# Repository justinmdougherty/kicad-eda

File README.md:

# dougherty-eda — Claude Code marketplace

Plugins for electronic design automation.

```
/plugin marketplace add justinmdougherty/kicad-eda
/plugin install kicad-eda@dougherty-eda
/kicad-eda:setup        # checks/installs KiCad, Java, Python
```

**New to all of this?** Start with the step-by-step
[setup guide](kicad-eda/docs/SETUP.md) — it assumes nothing and takes you
from a blank machine to your first board.

- **kicad-eda** — design circuit boards by chatting with Claude: describe the
  board, get back an ERC-clean schematic, a placed + autorouted PCB with
  clean DRC, and a fab-ready zip (Gerbers, drill, BOM, CPL). Five
  self-remediating review gates in the IEEE 15288.2 style do the engineering
  discipline; KiCad 10 + the bundled Freerouting autorouter do the file
  work, and an optional KiCad 11 nightly lets KiCad draw the schematic
  itself through its IPC API. See [`kicad-eda/README.md`](kicad-eda/README.md) to get started and
  [`kicad-eda/docs/PIPELINE.md`](kicad-eda/docs/PIPELINE.md) for the
  internals run-book.

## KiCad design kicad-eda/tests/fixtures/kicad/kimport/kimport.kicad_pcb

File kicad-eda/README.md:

# kicad-eda — Napkin to Gerbers

A Claude Code plugin that designs circuit boards **in conversation**. You
describe the board you want — what it does, how it's powered, what it
connects to — and Claude carries it from concept to a fab-ready zip:
schematic with clean ERC, placed and routed PCB with clean DRC (Claude
routes it net by net through KiCad's board API, or Freerouting does),
Gerbers, drill, BOM and placement files you can upload straight to JLCPCB.

```
You:    I need a USB-C powered 3-channel LED driver, 1.5 A per channel.
Claude: <asks the questions an engineer would, then designs it>
        … G1 requirements ✓  G2 schematic+ERC ✓  G3 placement ✓
        G4 routed, DRC 0/0 ✓  G5 fab package ✓ → led_driver_JLCPCB.zip
```

The work runs through **five formal review gates** (IEEE 15288.2 style) that
**self-remediate**: missing bypass caps get added, placement loosens itself
when routing is congested, routing micro-gaps and split power planes are
healed, under-ampacity layer transitions get parallel vias, dissipating
power packages get IPC-7093 thermal via farms. You only get asked when a
decision genuinely needs design intent.

## Install

> **First time? Never used Claude Code or cloned a repo?** Follow
> **[docs/SETUP.md](docs/SETUP.md)** — a step-by-step guide from a blank
> machine to your first board, no prior knowledge assumed.

```
/plugin marketplace add justinmdougherty/kicad-eda
/plugin install kicad-eda@dougherty-eda
```

Then run **`/kicad-eda:setup`** once — it checks the three external
dependencies and installs what's missing:

| Dependency | Used for | Windows | macOS |
|---|---|---|---|
| KiCad 10 | kicad-cli, bundled pcbnew Python, stock libraries | `winget install KiCad.KiCad` | `brew install --cask kicad` |
| KiCad 11 nightly *(optional)* | schematic API backend: KiCad draws the schematic itself, headless or live in its editor | [nightly installer](https://downloads.kicad.org/kicad/windows/explore/nightlies) (lands in `Program Files\KiCad\10.99`) | nightly `.dmg` from the same site |
| Java 17–21 | Freerouting 1.9.0 autorouter (jar is bundled) | `winget install EclipseAdoptium.Temurin.21.JRE` | `brew install --cask temurin@21` |
| Python 3.10+ | MCP server + pipeline harness | `winget install Python.Python.3.12` | `brew install python` |

Python *packages* need nothing: the server launcher
(`scripts/launch-server.js`) builds its own venv on first start and keeps it
in the plugin data dir, surviving updates. `setup` only reports the KiCad 11
nightly; it never installs it.

## Usage

Just talk to Claude about the board you want, or jump straight in:

```
/kicad-eda:pipeline a USB-C powered 3-channel LED driver, 1.5 A per channel
/kicad-eda:new-board ...     # GUI-assisted flow in the KiCad editor instead
```

You get back the full project: `netlist.json` (the design's source of
truth), `.kicad_sch`, `.kicad_pcb` (open them in KiCad), top/bottom renders
to eyeball, a design-intent report, and the fab zip.

Under the hood the conversation produces a pad-level `netlist.json`, and the
headless pipeline does the rest — schematic + ERC (through KiCad 11's
schematic API when a nightly is installed, else the plugin writes the file
itself), SWIG board build (placement, planes, preroutes, silk), routing,
DRC + IPC-2221/2141A checks, Gerber/BOM/CPL export. Power users can
author or edit `netlist.json` directly and run
`/kicad-eda:pipeline path/to/netlist.json`; the schema, gate map and the
schematic-backend rules live in **`docs/PIPELINE.md`** (the run-book).

**Routing is Claude's job, not an autorouter's.** With a KiCad 11 nightly
installed (or the board open in a running KiCad with its API server on),
Claude routes the placed board itself through KiCad's board API: it reads
pads, net classes, planes and the foreign copper near every unrouted link,
lays tracks and vias net by net, and clears real kicad-cli DRC in a repair
loop (`agent-routing` skill, `router` subagent). The tools:
`open_board`, `board_overview`, `board_pads`, `unrouted_connections`,
`route_net`, `add_vias`, `remove_routing`, `route_check`, `route_status`,
`save_board`, `close_board`, `list_open_boards`. Freerouting
(`autoroute_board`) stays as the fallback and is what the unattended
`run_pipeline.py` harness runs. One consequence to know: a board saved by the
headless KiCad 11 session becomes a **KiCad 11 file** — KiCad 9/10, their
kicad-cli/pcbnew and the Freerouting/SWIG tools cannot read it afterwards
(DRC and Gerbers still work through kicad-cli 11), so open it in KiCad 11.

## What's inside

| Component | What it does |
|---|---|
| `server/` | The `kicad-generator` MCP server (`kicad_env` finds every installed KiCad and picks one per job — board jobs follow the KiCad that wrote the file; `backends/` is the KiCad 11 IPC schematic backend and the board API backend (`pcb_api`) on the vendored `vendor/kipy`; `route_planner` + `board_route_tools` are the agent-routing geometry and tools; `sch_file_model` is the schematic file-writing fallback) + the toolchain it shells into: `sch_build` (ERC-clean schematics without KiCad 11), `swig_build_board` (placement/planes/preroutes/silk under KiCad's bundled Python), `netclass_writer` + `ipc_rules` (IPC-2221/2141A math), `swig_gate_checks` (placement/thermal/plane/height/routed-width/via-ampacity reviews), `swig_board_fixes` (auto-remediation incl. a BFS maze router), `silk_place`, `gates` + `remediate` (the review system), and `freerouting-1.9.0.jar`. |
| `pipeline/` | `run_pipeline.py` (one board through all five gates) and `run_all.py` (the developer regression suite over `examples/`). |
| `examples/` | Test netlists used to validate the process (QFN, LQFP, multi-unit op-amps, a 3 A buck, RF boards, an ESP32-C3 node, a two-sided RPi 5 HAT). Useful as schema references; not end-user content. |
| `docs/PIPELINE.md` | The run-book: netlist schema, gate map, env vars, and the known-traps list that costs real hours to rediscover. |
| `skills/` | `netlist-pipeline` (headless flow), `pcb-design` (GUI flow) and `agent-routing` (how Claude routes a board through the KiCad board API). |
| `agents/` | Gate reviewers: `parts-selector`, `erc-reviewer`, `placement-reviewer`, `drc-reviewer`, `fab-checker`; and `router`, the routing specialist that runs the route / DRC / repair loop. |
| `commands/` | `/setup`, `/pipeline`, `/new-board`, `/erc`, `/drc`, `/gerbers`. |
| `hooks/` | Cross-platform (Node): session env report, IPC-API guard for GUI tools, schematic structure check after writes. |

## Requirements

- **Claude Code or Claude Desktop** (local MCP server — not the web app).
- KiCad 10, Java 17–21, Python 3.10+ (see Install). KiCad 9 mostly works
  but the headless pipeline is validated against 10.
- **Optional: a KiCad 11 nightly** from
  <https://downloads.kicad.org/kicad/windows/explore/nightlies>. It installs
  beside KiCad 10 as `Program Files\KiCad\10.99` and enables the schematic
  API backend (`server_status().schematic_backend == "api"`) and the headless
  board API for agent routing (`server_status().board_api`). Open it once
  after installing — or copy `sym-lib-table` and `fp-lib-table` from
  `<install>\share\kicad\template` into `%APPDATA%\kicad\10.99` — or the
  headless server finds no libraries. Keep KiCad 10 for the board build (the
  nightly has no bundled pcbnew Python). Schematics and boards it saves are
  KiCad 11 files; KiCad 9/10 cannot open them (board DRC/Gerbers then run
  through the nightly's kicad-cli automatically).
- The headless pipeline never needs the KiCad GUI. The GUI flow's PCB tools
  require KiCad running with **Preferences → API → Enable KiCad API server**;
  with KiCad 11 the schematic tools also work live in the open editor.

## Developing

```bash
claude plugin validate ./kicad-eda --strict
node scripts/launch-server.js          # run the MCP server by hand
.venv/bin/python -m pytest -q          # unit tier (+ live KiCad 11 API tests when a nightly is present)
.venv/bin/python pipeline/run_all.py   # regression matrix (routes for many minutes)
docker build -t kicad-eda . && docker run --rm kicad-eda   # suite in the official KiCad container
```

CI runs the same regression suite on every push (`.github/workflows/regression.yml`).

## License

MIT

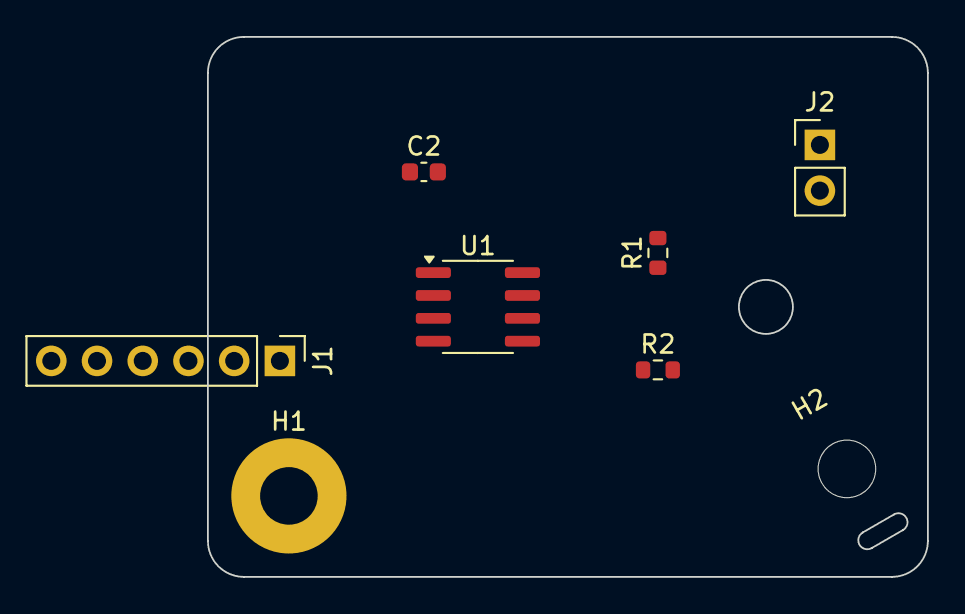
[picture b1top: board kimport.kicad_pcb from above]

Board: 2 copper layers, 40.0 x 30.0 mm, 9 parts (1 on the bottom side), 7 nets, no tracks yet.

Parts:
C1: 100nF; C_0603_1608Metric
C2: 1uF; C_0603_1608Metric
H1: MountingHole_3.2mm_M3_Pad
H2: MountingHole_3.2mm_M3
J1: IO; PinHeader_1x06_P2.54mm_Vertical
J2: AUX; PinHeader_1x02_P2.54mm_Vertical
R1: 1k; R_0603_1608Metric
R2: 10k; R_0603_1608Metric
U1: LM358; SOIC-8_3.9x4.9mm_P1.27mm

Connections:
/GND: C1.2, C2.2, H1.1, J1.2, J2.1, R2.2, U1.4
/IN_A: J1.3, R1.1
/IN_A_R: R1.2, U1.3
/IN_B: J1.5, R2.1, U1.5
/OUT_A: J1.4, U1.1, U1.2
/OUT_B: U1.6, U1.7
/P5V: C1.1, C2.1, J1.1, U1.8

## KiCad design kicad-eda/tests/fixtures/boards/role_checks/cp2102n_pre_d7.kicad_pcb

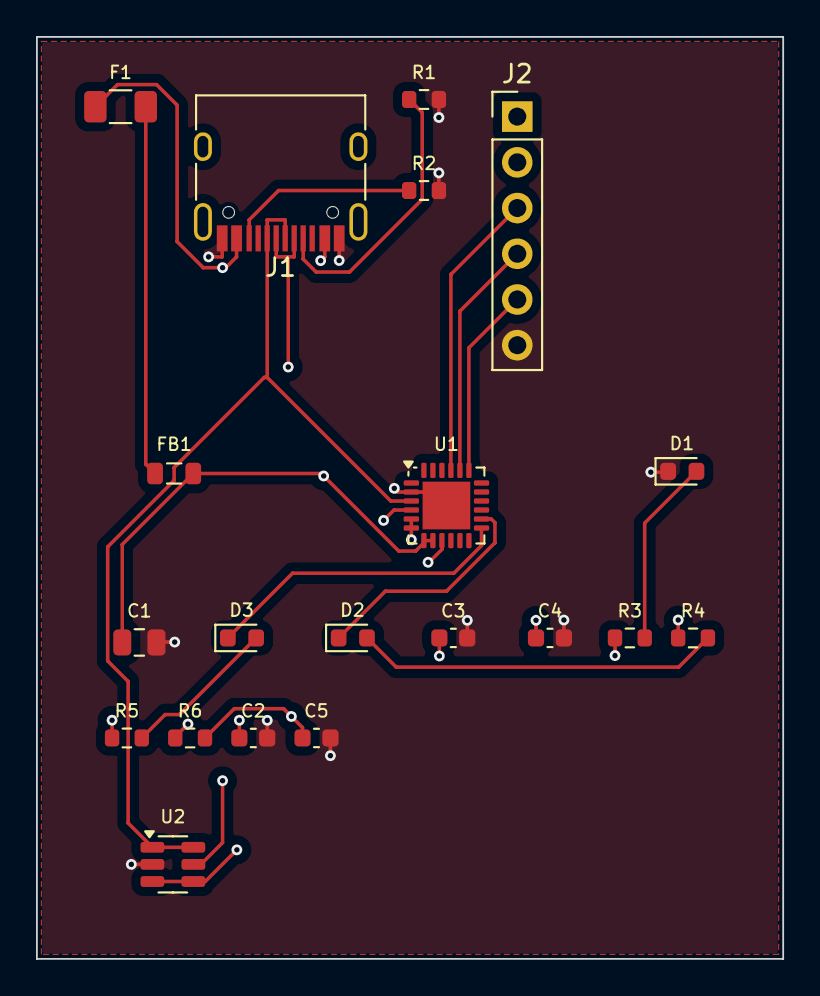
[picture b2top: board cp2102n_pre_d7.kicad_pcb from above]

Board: 4 copper layers, 41.5 x 51.2 mm, 20 parts (0 on the bottom side), 18 nets.

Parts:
C1: 4.7uF; C_0805_2012Metric
C2, C5: 1uF; C_0603_1608Metric
C3, C4: 100nF; C_0603_1608Metric
D1: PWR_GRN; LED_0603_1608Metric
D2: TX_YEL; LED_0603_1608Metric
D3: RX_GRN; LED_0603_1608Metric
F1: 500mA; Fuse_1206_3216Metric
FB1: 600R@100MHz; L_0805_2012Metric
J1: USB-C; USB_C_Receptacle_HRO_TYPE-C-31-M-12
J2: UART; PinHeader_1x06_P2.54mm_Vertical
R1, R2: 5.1k; R_0603_1608Metric
R3, R4, R5: 1k; R_0603_1608Metric
R6: 10k; R_0603_1608Metric
U1: CP2102N-A02-QFN24; QFN-24-1EP_4x4mm_P0.5mm_EP2.65x2.65mm
U2: USBLC6-2SC6; SOT-23-6

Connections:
+3V3: C2.1, C3.1, C4.1, J2.2, R3.1, R4.1, R5.1, R6.1, U1.5, U1.6
CC1: J1.A5, R1.1
CC2: J1.B5, R2.1
GND: C1.2, C2.2, C3.2, C4.2, C5.2, D1.1, J1.A1, J1.A12, J1.B1, J1.B12, J2.6, R1.2, R2.2, U1.2, U1.25, U2.2
PWR_LED_A: D1.2, R3.2
RST: C5.1, R6.2, U1.9
RTS: J2.5, U1.19
RXD: J2.4, U1.20
RXT_N: D3.1, U1.13
RX_LED_A: D3.2, R5.2
TXD: J2.3, U1.21
TXT_N: D2.1, U1.14
TX_LED_A: D2.2, R4.2
USB_DM: J1.A7, J1.B7, U1.4, U2.3, U2.4
USB_DP: J1.A6, J1.B6, U1.3, U2.1, U2.6
VBUS: F1.1, J1.A4, J1.A9, J1.B4, J1.B9, U2.5
VBUS_F: F1.2, FB1.1
VBUS_IN: C1.1, FB1.2, J2.1, U1.7, U1.8

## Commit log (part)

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2026-06-11 chore: baseline - gated headless pipeline, plugin packaging v0.2.0
2026-06-11 feat: thermal gate - dissipation vs package limits (G2) + EP via-farm check (G3)
    thermal_check.py: shunt I2R vs derated rating, FET conduction loss,
    linear-reg (Vin-Vout)*I, switcher loss estimate; Tj vs 80% Tj_max.
    Declared values block, estimates warn; per-part thermal overrides
    (p_diss/theta_ja/tj_max/i_max). G3 verifies >=4 thermal vias under
    dissipating exposed pads (IPC-7093). Example specs corrected where the
    gate caught real errors (AP2112K SOT-23-5 at 0.5A, LNA bias R at 4x
2026-06-11 feat: pre-route plane integrity check at G3
    Per plane net: union-find over fill islands + pads + preroute copper.
    True multi-island pad split = blocker (DSN export hides voids, router
    returns the net broken). Pinch corridors <1.8mm between pad groups
    (one router via from sealing) = warning, GND exempt (post-route pours
    own its unification). Pad-to-island attach uses true polygon distance
    (bbox distance is meaningless for a board-spanning outline). Gate
2026-06-11 feat: height keepout zones at G3 (mechanical ceiling)
    netlist height_zones: per-region max_height with side F/B/both and
    exempt list; part height from component 'height' or a package table.
    Over-ceiling = blocker, unknown-height-in-zone = warning. HAT example
    gains a 4mm B-side ceiling (clearance to the Pi) exempting J5.
2026-06-11 feat: diff-pair declaration + routed-as-pair flagging at G4
    net_specs {'diff_pair': partner, dp_tol_mm, dp_gap_mm}: measures
    intra-pair length mismatch and coupled-length fraction (<70% flags).
    Warning-grade by design (Freerouting cannot pair-route; preroute real
    pairs). cp2102n example declares USB_DP/USB_DM — its routed board
    honestly reports 1.64mm mismatch, 55% coupled. G4 verdict now carries
    the gate-check warnings channel.
2026-06-11 feat: EMC stitching wired into G4 (opt-in netlist 'emc' block)
    After G4 passes: perimeter GND via fence + interior grid via
    emc_stitch.py (lambda/20 pitch from max_freq_hz, else 3mm), then
    re-DRC — verified 35 vias on lm358 with DRC staying 0/0. Teardrops:
    KiCad 10 exposes no headless API (documented as known trap; request
    emits a GUI reminder).
2026-06-11 feat: auto-render top/bottom at gate exits
    Placement view (basic quality) rendered right after G3 passes, final
    board (high quality) at G5; paths in report renders_placement /
    renders_final. Every gate exit leaves a visual record without hand-run
    kicad-cli.
2026-06-11 feat: BOM sourcing audit at G5
    Every assembly-relevant part must carry lcsc or mpn (TP/H/FID exempt);
    LCSC format validated. Warning by default, netlist require_sourcing:
    true upgrades to release blocker. HAT honestly reports 63 unsourced
    parts in soft mode.
2026-06-11 feat: route cache - skip build+route when nothing moves copper
    Hash of geometry/nets/net_specs/preroutes/board/emc written to
    <netlist>.cache.json after G4 passes; a matching re-run reuses the
    routed board and goes straight to gates/checks/fab (gates still re-run
    against the artifact - cache skips work, never judgement). Computed
    after G2 so netlist remediation invalidates; PIPELINE_NO_CACHE=1
    bypasses. Verified: lm358 full pipeline PASS via cache with zero
2026-06-11 feat: negative fixtures proving G3 detection + G4 healing every run
    negative_g3 (router-free, fails AT G3 by design): inward-mouth USB-C
    blocker + a 2x20 THT wall pinching the +3V3 plane (corridors ~1.2mm)
    — asserts both findings. negative_g4_heal: cuts the longest signal
    track on a copy of routed lm358, asserts the healer restores DRC to
    0/0 without the router. Fixture-driven fixes: plane check now
    UNFRACTUREs fills (KiCad stores holes as slits - HoleCount()==0);
2026-06-11 refactor: split swig_build_board into engine/shapes/orchestrator, pin deps
    swig_build_board.py (749 lines) was three modules in one file. Extracted:
    - place_engine.py — courtyard-aware shelf packing, functional clustering,
    connector edge handling (pure placement math)
    - board_shapes.py — outline, copper planes, keep-out rule areas
    - swig_build_board.py keeps loading, net assignment, and orchestration
    Verified placement-identical: lm358/cp2102n/HAT rebuilt before and after,
2026-06-11 ci: GitHub Actions regression workflow + self-contained Docker image
    .github/workflows/regression.yml — runs the gated 10-board matrix plus
    negative fixtures in the official kicad/kicad:10.0 container (kicad-cli +
    pcbnew SWIG python, the exact runtime the headless pipeline shells into).
    Installs only a JRE for the bundled Freerouting 1.9.0 and a venv from
    server/requirements.txt. Uploads board artifacts on failure. Triggers:
    push to main/improvements, PRs, manual dispatch.
2026-06-11 fix: EP thermal-via auto-remedy + routed-aware cache re-validation
    The first fully-routed regression run after the 11-item pass exposed two
    gaps; both are fixed and the 12-line matrix is now ALL PASS (ERC 0, DRC
    0/0, 0 unconnected on all 10 boards; both negative fixtures detect/heal).
    1. G3 EP via-farm blocker had no auto-remedy. buck_5v3a and
    negative_gate_test use the LM2596 in a plain TO-263 footprint -- a
    real dissipator with zero thermal vias, and the library has no
2026-06-11 chore: untrack run-artifact logs/, add repo-root .gitignore
2026-06-11 chore: bump plugin to v0.3.0
    Thermal gate, plane integrity, height zones, diff-pair flagging, EMC
    stitch in G4, EP via-farm auto-remedy, route cache, sourcing audit,
    auto-renders, negative fixtures, CI + Docker, builder refactor.
2026-06-11 chore: point manifest URLs at justinmdougherty/kicad-eda, sync versions
2026-06-11 docs: lead the READMEs with the chat-driven design experience
    The product is: describe your board in conversation, get a fab-ready
    zip. The netlist.json schema and regression suite are internals for
    power users and developers. Front doors now say so, examples/ is marked
    as test fixtures, and install slugs point at the real repo.
2026-06-11 docs: zero-knowledge SETUP.md walkthrough
    Step-by-step from a blank machine to a first board: accept the GitHub
    invite, install Git/Claude Code/KiCad 10/Java/Python (winget + brew
    commands, new-terminal gotchas, Windows fake-python trap), clone once to
    cache GitHub credentials for the private repo, plugin install + restart,
    /setup verification, a first-board walkthrough with expectations
    (questions, gate flow, router runtime, permission prompts) and an output
2026-06-11 fix: make the pipeline run on display-less Linux (CI/Docker)
    The first cloud CI run failed everywhere; reproduced and fixed locally
    in the same kicad/kicad:10.0 container CI uses, then proven by a full
    five-gate lm358 run (routed, DRC 0/0) inside it.
    1. requirements.txt was missing sexpdata (sch_build + the netlist lint
    import it) -- present on the dev venv from ad-hoc installs, never
    pinned, so every board died at G2 with schematic generation failed.
